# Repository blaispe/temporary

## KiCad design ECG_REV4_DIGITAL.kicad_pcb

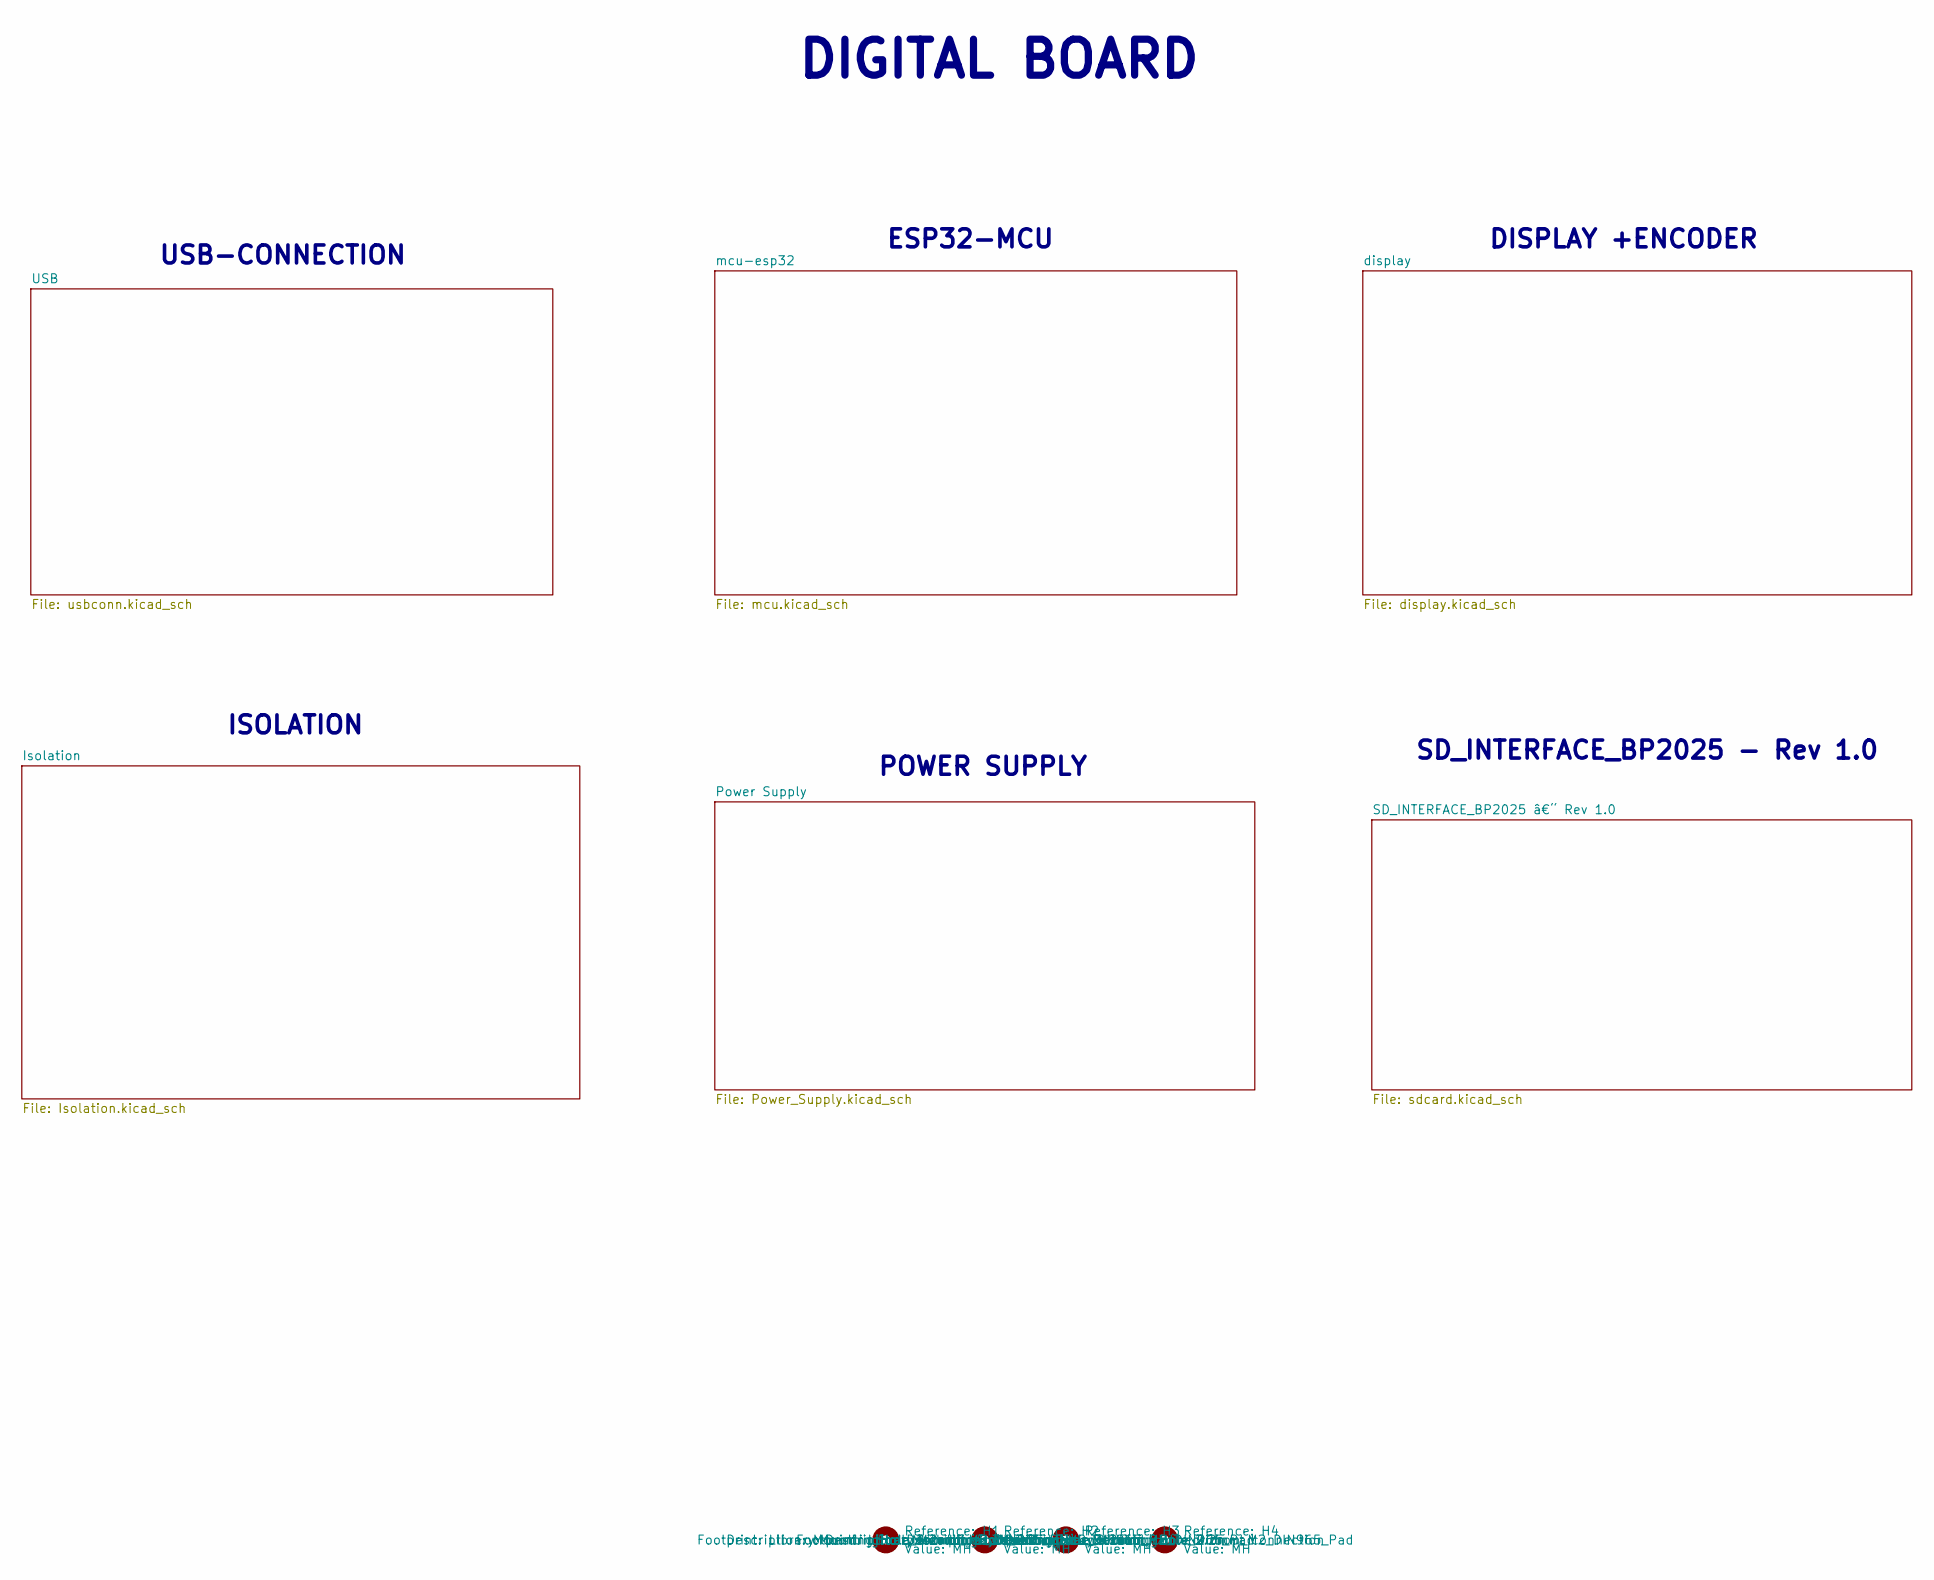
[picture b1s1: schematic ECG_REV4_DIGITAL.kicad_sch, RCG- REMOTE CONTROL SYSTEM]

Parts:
H1, H2, H3, H4: MH; MountingHole_2.2mm_M2_DIN965_Pad

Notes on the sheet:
POWER SUPPLY
DISPLAY +ENCODER
USB-CONNECTION
SD_INTERFACE_BP2025 - Rev 1.0
ESP32-MCU
ISOLATION
DIGITAL BOARD

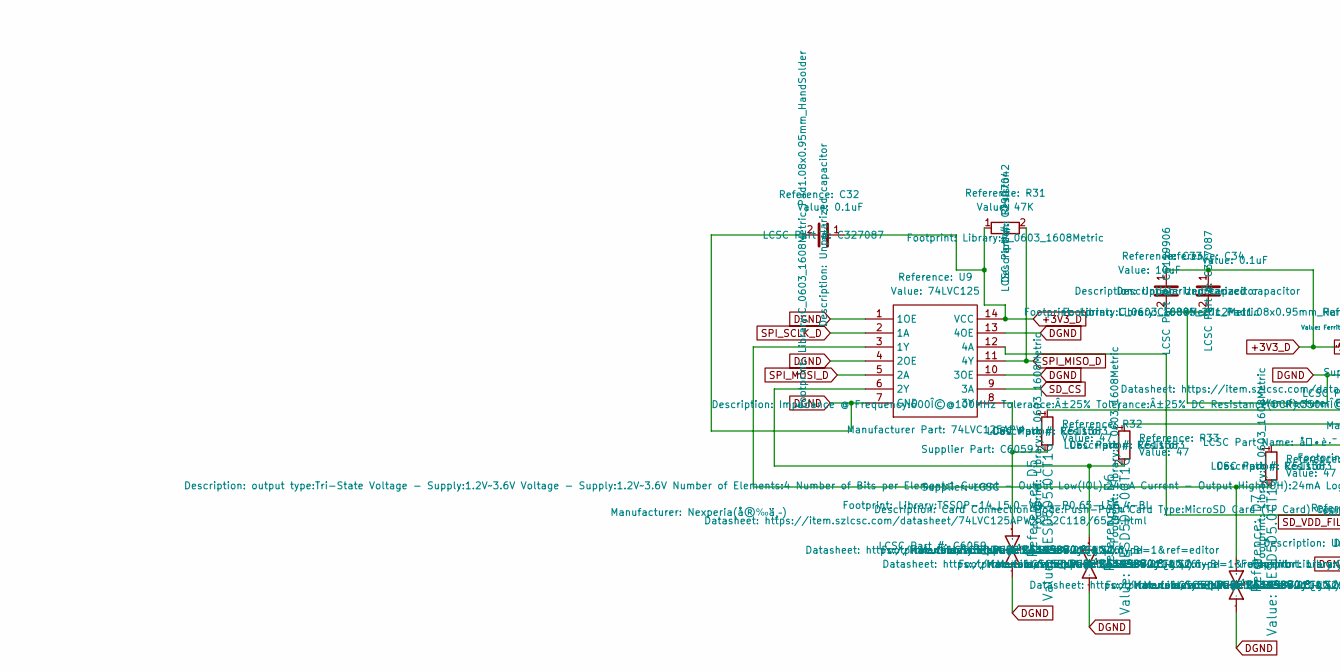
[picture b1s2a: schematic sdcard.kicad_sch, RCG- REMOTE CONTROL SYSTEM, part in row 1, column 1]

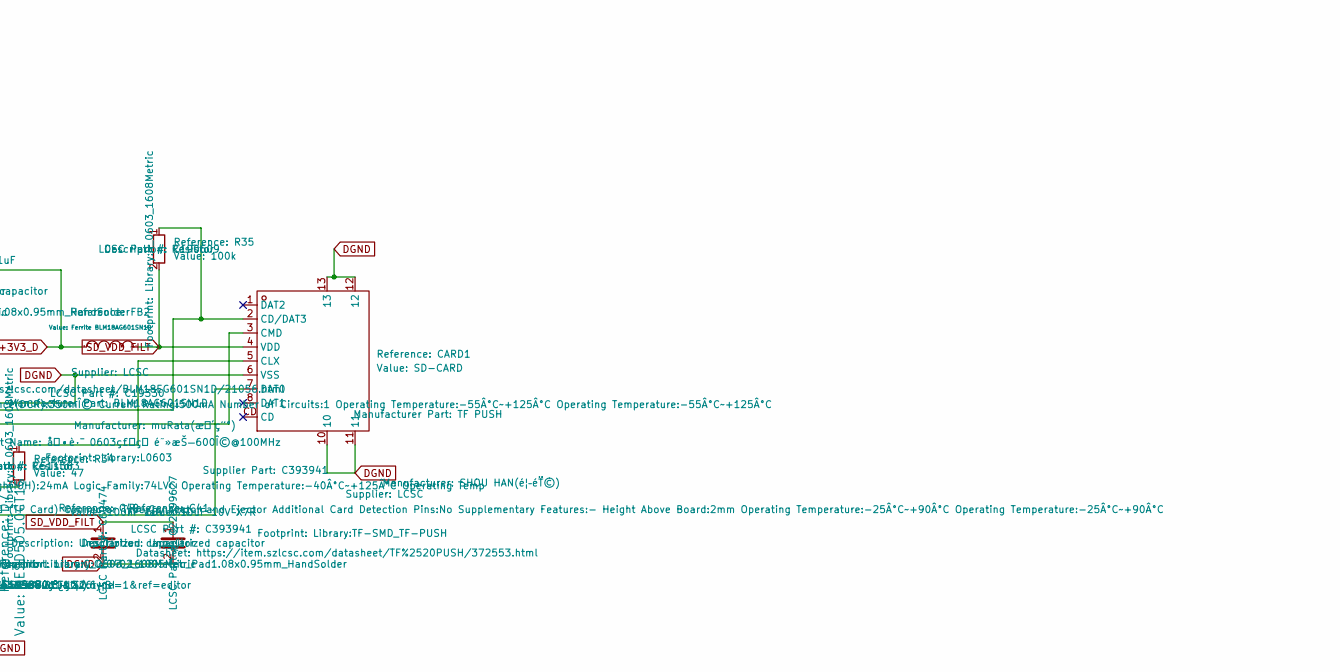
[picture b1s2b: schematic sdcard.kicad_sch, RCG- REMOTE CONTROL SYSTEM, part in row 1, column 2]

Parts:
C32, C34: 0.1uF; C_0603_1608Metric_Pad1.08x0.95mm_HandSolder; LCSC Part # C327087
C33: 10uF; C_0805_2012Metric; LCSC Part # C6119906
C40: 100nF 16V X7R; C_0402_1005Metric; LCSC Part # C60474
C41: 10uF 10V X7R; C_0603_1608Metric_Pad1.08x0.95mm_HandSolder; LCSC Part # C22399627
CARD1: SD-CARD; TF-SMD_TF-PUSH; Manufacturer Part TF PUSH; LCSC Part # C393941
D5, D6, D7: LESD5D5.0CT1G; SOD-523_L1.2-W0.8-LS1.6-BI; Manufacturer Part LESD5D5.0CT1G; LCSC Part # C5199850
FB2: Ferrite BLM18AG601SN1D; L0603; Manufacturer Part BLM18AG601SN1D; LCSC Part # C19330
R31: 47K; R_0603_1608Metric; LCSC Part # C2907042
R32, R33, R34: 47; R_0603_1608Metric; LCSC Part # C511383
R35: 100k; R_0603_1608Metric; LCSC Part # C190609
U9: 74LVC125; TSSOP-14_L5.0-W4.4-P0.65-LS6.4-BL; Manufacturer Part 74LVC125APW; LCSC Part # C6059

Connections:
+3V3_D: C32.1, C33.1, C34.1, FB2.1, R31.1, U9.14 (VCC); also elsewhere on the board
DGND: C32.2, C33.2, C34.2, C40.2, C41.2, CARD1.6 (VSS), CARD1.10, CARD1.11, CARD1.12, CARD1.13, D5.2, D6.2, D7.2, U9.1 (1OE), U9.4 (2OE), U9.7 (GND), U9.10 (3OE), U9.13 (4OE); also elsewhere on the board
unnamed: CARD1.2 (CD/DAT3), R32.1, R35.1
unnamed: CARD1.5 (CLX), R34.1
unnamed: CARD1.3 (CMD), R33.1
unnamed: CARD1.7 (DAT0), U9.12 (4A)
unnamed: D7.1, R34.2, U9.3 (1Y)
unnamed: D6.1, R33.2, U9.6 (2Y)
unnamed: D5.1, R32.2, U9.8 (3Y)
SD_CS: U9.9 (3A); also elsewhere on the board
SD_VDD_FILT: C40.1, C41.1, CARD1.4 (VDD), FB2.2, R35.2
SPI_MISO_D: R31.2, U9.11 (4Y); also elsewhere on the board
SPI_MOSI_D: U9.5 (2A); also elsewhere on the board
SPI_SCLK_D: U9.2 (1A); also elsewhere on the board

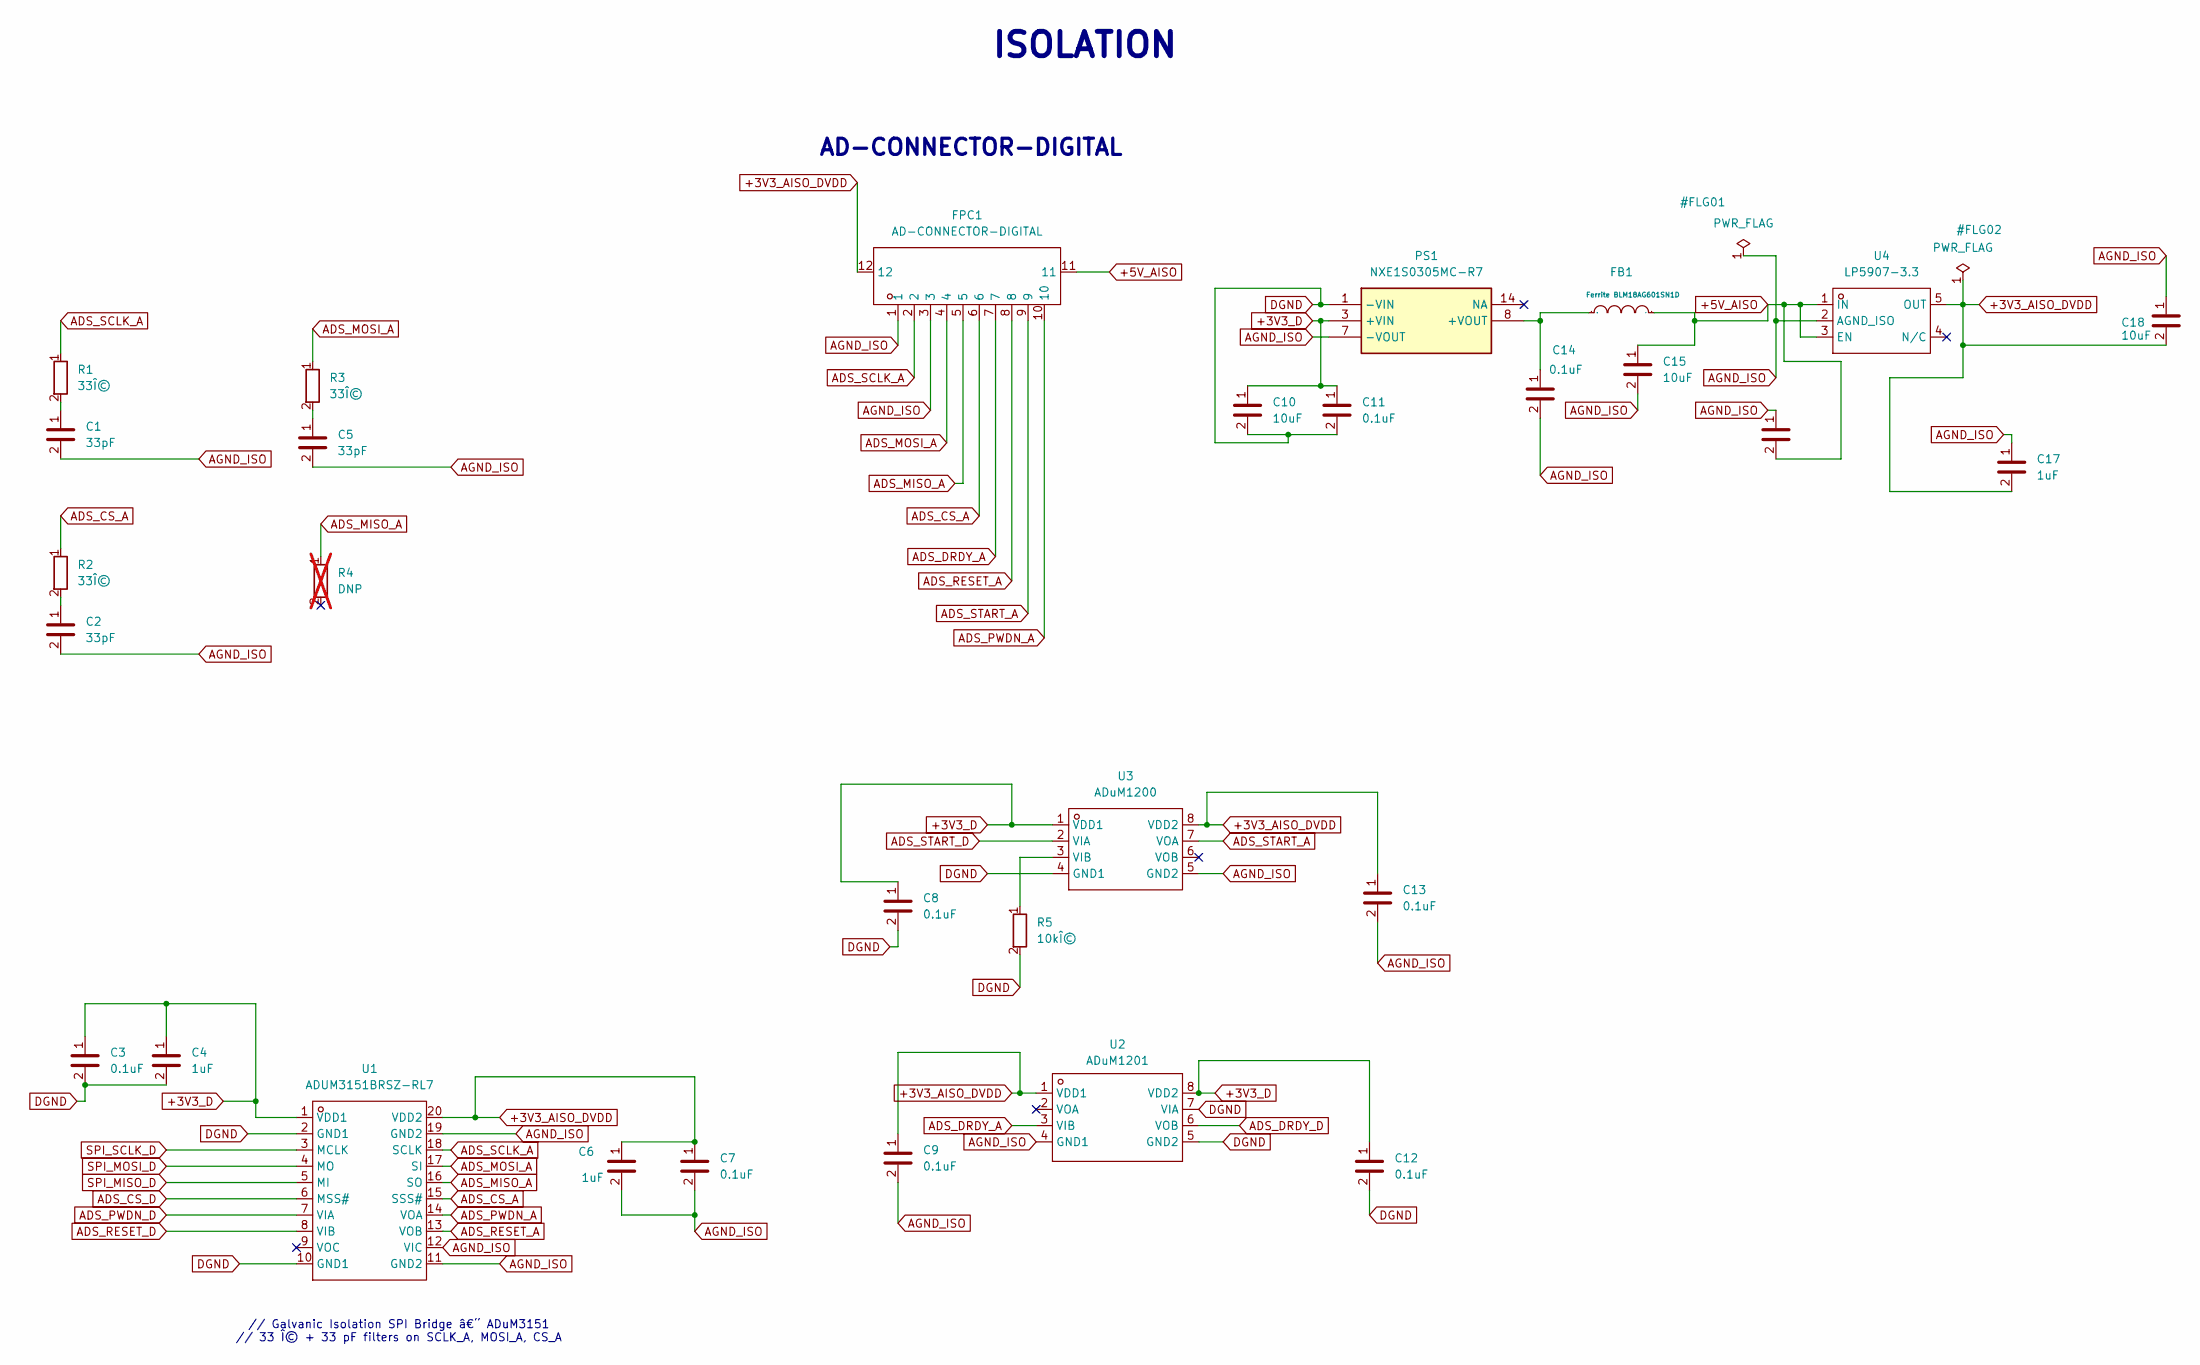
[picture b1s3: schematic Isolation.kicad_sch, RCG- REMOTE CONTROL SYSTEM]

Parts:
C1, C2, C5: 33pF; C_0603_1608Metric; LCSC Part # C1663
C3, C7, C8, C9, C11, C12, C13, C14: 0.1uF; C_0603_1608Metric; LCSC Part # C1591
C4, C6, C16, C17: 1uF; C_0603_1608Metric; LCSC Part # C29936
C10, C15, C18: 10uF; C_0603_1608Metric; LCSC Part # C380314
FB1: Ferrite BLM18AG601SN1D; L0603; Manufacturer Part BLM18AG601SN1D; LCSC Part # C19330
FPC1: AD-CONNECTOR-DIGITAL; FPC-SMD_12P-P0.50_XUNPU_FPC-05F-12PH20; Manufacturer Part FPC-05F-12PH20; LCSC Part # C2856799
PS1: NXE1S0305MC-R7; NXE1S0303MCR7; Manufacturer_Part_Number NXE1S0305MC-R7; Mouser Part Number 580-NXE1S0305MC-R7
R1, R2, R3: 33Î©; R_0603_1608Metric; LCSC Part # C23140
R4: DNP; R_0603_1608Metric; LCSC Part # C23140; not fitted
R5: 10kÎ©; R_0603_1608Metric; LCSC Part # C98220
U1: ADUM3151BRSZ-RL7; SSOP-20L_L7.2-W5.3-P0.65-LS7.8-BL; Manufacturer Part ADUM3151BRSZ-RL7; LCSC Part # C579398
U2: ADuM1201; SOIC-8_L4.9-W3.9-P1.27-LS6.0-BL; Manufacturer Part ADUM1201BRZ; LCSC Part # C87626
U3: ADuM1200; SOIC-8_L4.9-W3.9-P1.27-LS6.0-BL; Manufacturer Part ADUM1200BRZ-RL7; LCSC Part # C30230
U4: LP5907-3.3; SOT-23-5_L3.0-W1.7-P0.95-LS2.8-BR; Manufacturer Part LP5907MFX-3.3/NOPB; LCSC Part # C80670

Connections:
+3V3_AISO_DVDD: C6.1, C7.1, C9.1, C13.1, C17.2, C18.2, FPC1.12, U1.20 (VDD2), U2.1 (VDD1), U3.8 (VDD2), U4.5 (OUT)
+3V3_D: C3.1, C4.1, C8.1, C10.1, C11.1, C12.1, PS1.3 (+VIN), U1.1 (VDD1), U2.8 (VDD2), U3.1 (VDD1); also elsewhere on the board
+5V_AISO: C15.1, C16.2, FB1.2, FPC1.11, U4.1 (IN), U4.3 (EN)
ADS_CS_A: FPC1.6, R2.1, U1.15 (SSS#)
ADS_CS_D: U1.6 (MSS#); also elsewhere on the board
ADS_DRDY_A: FPC1.7, U2.3 (VIB)
ADS_DRDY_D: U2.6 (VOB); also elsewhere on the board
ADS_MISO_A: FPC1.5, R4.1, U1.16 (SO)
ADS_MOSI_A: FPC1.4, R3.1, U1.17 (SI)
ADS_PWDN_A: FPC1.10, U1.14 (VOA)
ADS_PWDN_D: U1.7 (VIA); also elsewhere on the board
ADS_RESET_A: FPC1.8, U1.13 (VOB)
ADS_RESET_D: U1.8 (VIB); also elsewhere on the board
ADS_SCLK_A: FPC1.2, R1.1, U1.18 (SCLK)
ADS_START_A: FPC1.9, U3.7 (VOA)
ADS_START_D: U3.2 (VIA); also elsewhere on the board
AGND_ISO: C1.2, C2.2, C5.2, C6.2, C7.2, C9.2, C13.2, C14.2, C15.2, C16.1, C17.1, C18.1, FPC1.1, FPC1.3, PS1.7 (-VOUT), U1.11 (GND2), U1.12 (VIC), U1.19 (GND2), U2.4 (GND1), U3.5 (GND2), U4.2 (AGND_ISO)
DGND: C3.2, C4.2, C8.2, C10.2, C11.2, C12.2, PS1.1 (-VIN), R5.2, U1.2 (GND1), U1.10 (GND1), U2.5 (GND2), U2.7 (VIA), U3.4 (GND1); also elsewhere on the board
unnamed: C1.1, R1.2
unnamed: C2.1, R2.2
unnamed: C5.1, R3.2
unnamed: C14.1, FB1.1, PS1.8 (+VOUT)
unnamed: R5.1, U3.3 (VIB)
SPI_MISO_D: U1.5 (MI); also elsewhere on the board
SPI_MOSI_D: U1.4 (MO); also elsewhere on the board
SPI_SCLK_D: U1.3 (MCLK); also elsewhere on the board

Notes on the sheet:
// Galvanic Isolation SPI Bridge â€“ ADuM3151 // 33 Î© + 33 pF filters on SCLK_A, MOSI_A, CS_A
ISOLATION
AD-CONNECTOR-DIGITAL

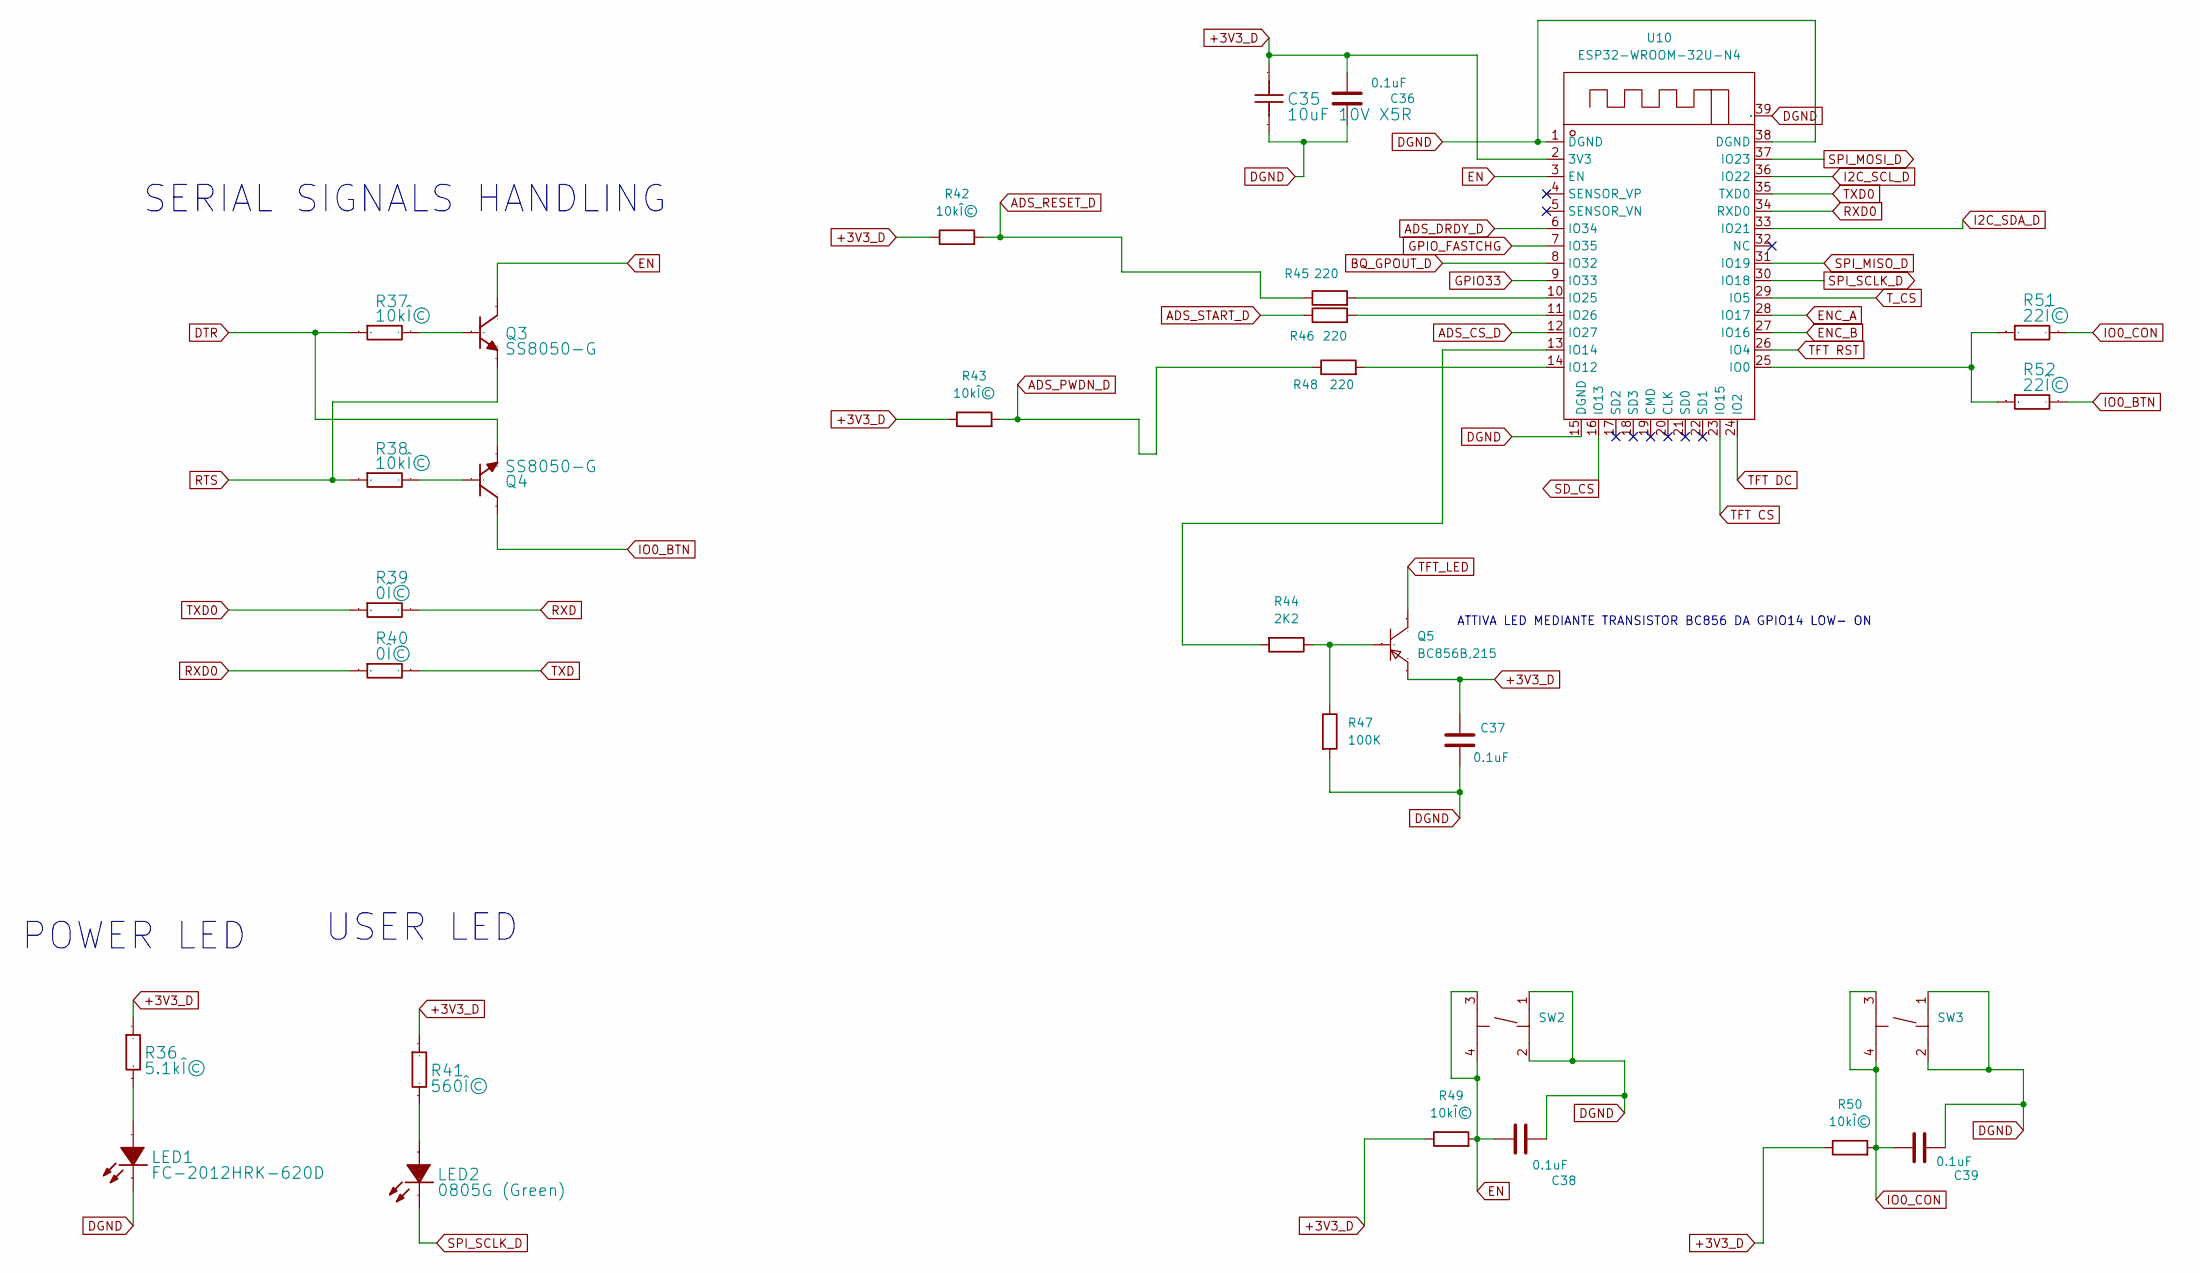
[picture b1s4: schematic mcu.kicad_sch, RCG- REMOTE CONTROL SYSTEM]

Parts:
C35: 10uF 10V X5R; C_0603_1608Metric_Pad1.08x0.95mm_HandSolder; Manufacturer Part CL10A106KP8NNNC; LCSC Part # C19702
C36, C38, C39: 0.1uF; C_0603_1608Metric_Pad1.08x0.95mm_HandSolder; LCSC Part # C1591
C37: 0.1uF; C_0603_1608Metric_Pad1.08x0.95mm_HandSolder; LCSC Part # C14663
LED1: FC-2012HRK-620D; LED0805-R-RD; Manufacturer Part NCD0805R1; LCSC Part # C84256
LED2: 0805G (Green); LED0805-R-RD; Manufacturer Part KT-0805ç¿ ç»¿; LCSC Part # C2297
Q3, Q4: SS8050-G; SOT-23-3_L2.9-W1.3-P1.90-LS2.4-BR; Manufacturer Part SS8050-G; LCSC Part # C164886
Q5: BC856B,215; SOT-23-3_L2.9-W1.6-P1.90-LS2.8-BR; Manufacturer Part BC856B,215; LCSC Part # C20069136
R36: 5.1kÎ©; R_0603_1608Metric_Pad0.98x0.95mm_HandSolder; LCSC Part # C2907044
R37, R38, R42, R43, R49, R50: 10kÎ©; R_0603_1608Metric_Pad0.98x0.95mm_HandSolder; LCSC Part # C98220
R39, R40: 0Î©; R_0603_1608Metric_Pad0.98x0.95mm_HandSolder; LCSC Part # C95177
R41: 560Î©; R_0603_1608Metric_Pad0.98x0.95mm_HandSolder; LCSC Part # C23204
R44: 2K2; R_0603_1608Metric_Pad0.98x0.95mm_HandSolder; LCSC Part # C114662
R45, R46, R48: 220; R_0603_1608Metric_Pad0.98x0.95mm_HandSolder; LCSC Part # C22962
R47: 100K; R_0603_1608Metric_Pad0.98x0.95mm_HandSolder; LCSC Part # C14675
R51, R52: 22Î©; R_0603_1608Metric_Pad0.98x0.95mm_HandSolder; LCSC Part # C23345
SW2, SW3: Microswitch; Manufacturer Part TS-1187A-B-A-B; LCSC Part # C318884
U10: ESP32-WROOM-32U-N4; WROOM-32U; Manufacturer Part ESP32-WROOM-32U-N4; LCSC Part # C328062

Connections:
+3V3_D: C35.2, C36.1, C37.1, Q5.2 (E), R36.2, R41.2, R42.1, R43.1, R49.1, R50.1, U10.2 (3V3); also elsewhere on the board
ADS_CS_D: U10.12 (IO27); also elsewhere on the board
ADS_DRDY_D: U10.6 (IO34); also elsewhere on the board
ADS_PWDN_D: R43.2, R48.1; also elsewhere on the board
ADS_RESET_D: R42.2, R45.1; also elsewhere on the board
ADS_START_D: R46.1; also elsewhere on the board
BQ_GPOUT_D: U10.8 (IO32); also elsewhere on the board
DGND: C35.1, C36.2, C37.2, C38.2, C39.2, LED1.1 (-), R47.2, SW2.1 (A), SW2.2 (B), SW3.1 (A), SW3.2 (B), U10.1 (DGND), U10.15 (DGND), U10.38 (DGND), U10.39 (DGND); also elsewhere on the board
DTR: Q4.2 (E), R37.1; also elsewhere on the board
EN: C38.1, Q3.3 (C), R49.2, SW2.3 (C), SW2.4 (D), U10.3 (EN)
ENC_A: U10.28 (IO17); also elsewhere on the board
ENC_B: U10.27 (IO16); also elsewhere on the board
GPIO33: U10.9 (IO33); also elsewhere on the board
GPIO_FASTCHG: U10.7 (IO35); also elsewhere on the board
I2C_SCL_D: U10.36 (IO22); also elsewhere on the board
I2C_SDA_D: U10.33 (IO21); also elsewhere on the board
IO0_BTN: Q4.3 (C), R52.2
IO0_CON: C39.1, R50.2, R51.2, SW3.3 (C), SW3.4 (D)
unnamed: LED1.2 (+), R36.1
unnamed: LED2.1 (A), R41.1
unnamed: Q3.1 (B), R37.2
unnamed: Q4.1 (B), R38.2
unnamed: Q5.1 (B), R44.1, R47.1
unnamed: R51.1, R52.1, U10.25 (IO0)
unnamed: R48.2, U10.14 (IO12)
unnamed: R44.2, U10.13 (IO14)
unnamed: R45.2, U10.10 (IO25)
unnamed: R46.2, U10.11 (IO26)
RTS: Q3.2 (E), R38.1; also elsewhere on the board
RXD: R39.2; also elsewhere on the board
RXD0: R40.1, U10.34 (RXD0)
SD_CS: U10.16 (IO13); also elsewhere on the board
SPI_MISO_D: U10.31 (IO19); also elsewhere on the board
SPI_MOSI_D: U10.37 (IO23); also elsewhere on the board
SPI_SCLK_D: LED2.2 (K), U10.30 (IO18); also elsewhere on the board
TFT CS: U10.23 (IO15); also elsewhere on the board
TFT DC: U10.24 (IO2); also elsewhere on the board
TFT RST: U10.26 (IO4); also elsewhere on the board
TFT_LED: Q5.3 (C); also elsewhere on the board
TXD: R40.2; also elsewhere on the board
TXD0: R39.1, U10.35 (TXD0)
T_CS: U10.29 (IO5); also elsewhere on the board

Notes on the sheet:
USER LED
POWER LED
SERIAL SIGNALS HANDLING
ATTIVA LED MEDIANTE TRANSISTOR BC856 DA GPIO14 LOW- ON

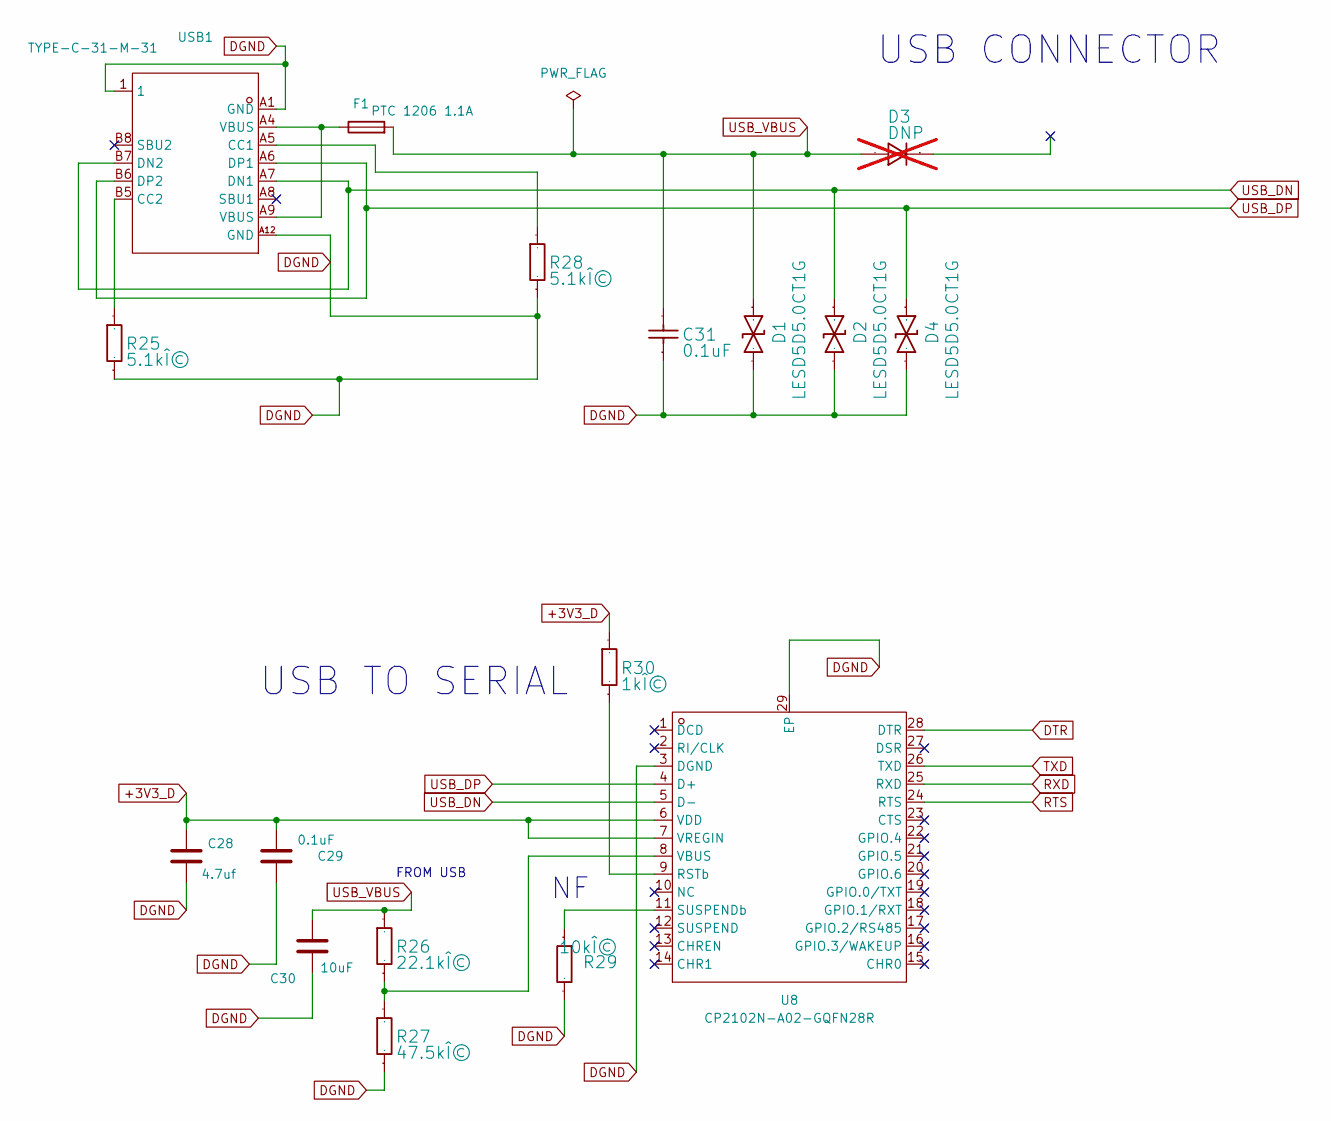
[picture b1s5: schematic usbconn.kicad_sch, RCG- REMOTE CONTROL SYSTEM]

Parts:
C28: 4.7uf; C_0603_1608Metric_Pad1.08x0.95mm_HandSolder; LCSC Part # C109456
C29: 0.1uF; C_0603_1608Metric_Pad1.08x0.95mm_HandSolder; LCSC Part # C1591
C30: 10uF; C_0603_1608Metric; LCSC Part # C380314
C31: 0.1uF; C_0603_1608Metric; LCSC Part # C1591
D1, D2, D4: LESD5D5.0CT1G; SOD-523_L1.2-W0.8-LS1.6-BI; Manufacturer Part LESD5D5.0CT1G; LCSC Part # C5199850
D3: DNP; SOD-323_L1.8-W1.3-LS2.5-RD; Manufacturer Part BAT20JFILM; LCSC Part # C155590; not fitted
F1: PTC 1206 1.1A; Fuse_1206_3216Metric; LCSC Part # C2803344
R25, R28: 5.1kÎ©; R_0603_1608Metric_Pad0.98x0.95mm_HandSolder; LCSC Part # C2907044
R26: 22.1kÎ©; R_0603_1608Metric_Pad0.98x0.95mm_HandSolder; LCSC Part # C2960862
R27: 47.5kÎ©; R_0603_1608Metric_Pad0.98x0.95mm_HandSolder; LCSC Part # C2933225
R29: 10kÎ©; R_0603_1608Metric_Pad0.98x0.95mm_HandSolder; LCSC Part # C98220
R30: 1kÎ©; R_0603_1608Metric_Pad0.98x0.95mm_HandSolder; LCSC Part # C21190
U8: CP2102N-A02-GQFN28R; QFN-28_L5.0-W5.0-P0.50-TL-EP3.3; Manufacturer Part CP2102N-A02-GQFN28R; LCSC Part # C964632
USB1: TYPE-C-31-M-31; USB-C-SMD_TYPE-C-31-M-31; Manufacturer Part TYPE-C-31-M-31; LCSC Part # C2760486

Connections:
+3V3_D: C28.1, C29.1, R30.2, U8.6 (VDD), U8.7 (VREGIN); also elsewhere on the board
DGND: C28.2, C29.2, C30.2, C31.1, D1.2, D2.2, D4.2, R25.1, R27.1, R28.1, R29.2, U8.3 (DGND), U8.29 (EP), USB1.1, USB1.A1 (GND), USB1.A12 (GND); also elsewhere on the board
DTR: U8.28 (DTR); also elsewhere on the board
unnamed: F1.1, USB1.A4 (VBUS), USB1.A9 (VBUS)
unnamed: R30.1, U8.9 (RSTb)
unnamed: R29.1, U8.11 (SUSPENDb)
unnamed: R26.1, R27.2, U8.8 (VBUS)
unnamed: R28.2, USB1.A5 (CC1)
unnamed: R25.2, USB1.B5 (CC2)
RTS: U8.24 (RTS); also elsewhere on the board
RXD: U8.25 (RXD); also elsewhere on the board
TXD: U8.26 (TXD); also elsewhere on the board
USB_DN: D2.1, U8.5 (D-), USB1.A7 (DN1), USB1.B7 (DN2)
USB_DP: D4.1, U8.4 (D+), USB1.A6 (DP1), USB1.B6 (DP2)
USB_VBUS: C30.1, C31.2, D1.1, D3.2 (A_2), F1.2, R26.2; also elsewhere on the board

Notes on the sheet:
USB CONNECTOR
USB TO SERIAL
FROM USB

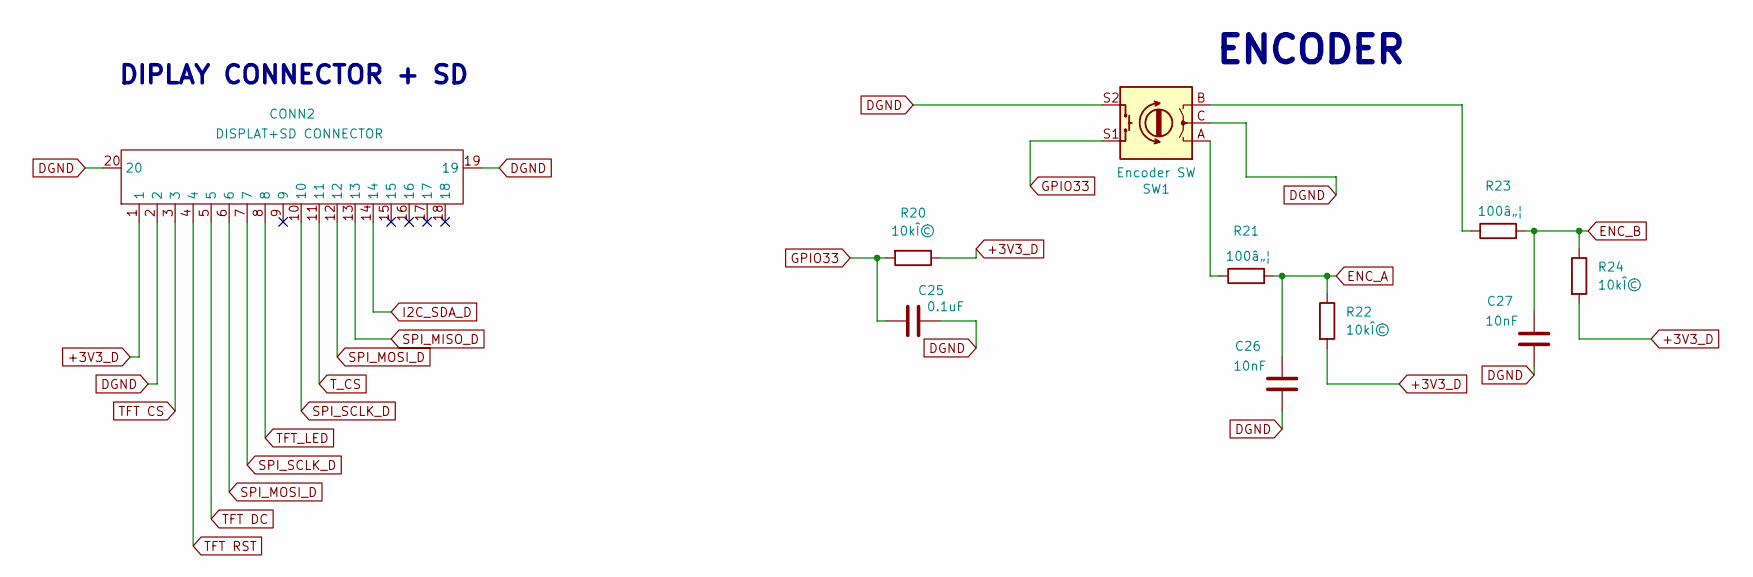
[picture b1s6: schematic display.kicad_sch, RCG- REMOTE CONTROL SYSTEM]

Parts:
C25: 0.1uF; C_0603_1608Metric_Pad1.08x0.95mm_HandSolder; LCSC Part # C1591
C26, C27: 10nF; C_0603_1608Metric_Pad1.08x0.95mm_HandSolder; LCSC Part # C100042
CONN2: DISPLAT+SD CONNECTOR; FPC-SMD_18P-P0.50_HC-FPC-0.5-18P-CXH20; Manufacturer Part FPC02-S0.5-18AH2.0; LCSC Part # C19267915
R20, R22, R24: 10kÎ©; R_0603_1608Metric_Pad0.98x0.95mm_HandSolder; LCSC Part # C98220
R21, R23: 100â„¦; R_0603_1608Metric_Pad0.98x0.95mm_HandSolder; LCSC Part # C105588
SW1: Encoder SW; RotaryEncoder_Alps_EC11E-Switch_Vertical_Modified_H20mm

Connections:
+3V3_D: CONN2.1, R20.1, R22.2, R24.2; also elsewhere on the board
DGND: C25.2, C26.2, C27.2, CONN2.2, CONN2.19, CONN2.20, SW1.C, SW1.S2; also elsewhere on the board
ENC_A: C26.1, R21.2, R22.1; also elsewhere on the board
ENC_B: C27.1, R23.2, R24.1; also elsewhere on the board
GPIO33: C25.1, R20.2, SW1.S1; also elsewhere on the board
I2C_SDA_D: CONN2.14; also elsewhere on the board
unnamed: R21.1, SW1.A
unnamed: R23.1, SW1.B
SPI_MISO_D: CONN2.13; also elsewhere on the board
SPI_MOSI_D: CONN2.6, CONN2.12; also elsewhere on the board
SPI_SCLK_D: CONN2.7, CONN2.10; also elsewhere on the board
TFT CS: CONN2.3; also elsewhere on the board
TFT DC: CONN2.5; also elsewhere on the board
TFT RST: CONN2.4; also elsewhere on the board
TFT_LED: CONN2.8; also elsewhere on the board
T_CS: CONN2.11; also elsewhere on the board

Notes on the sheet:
DIPLAY CONNECTOR + SD
ENCODER
